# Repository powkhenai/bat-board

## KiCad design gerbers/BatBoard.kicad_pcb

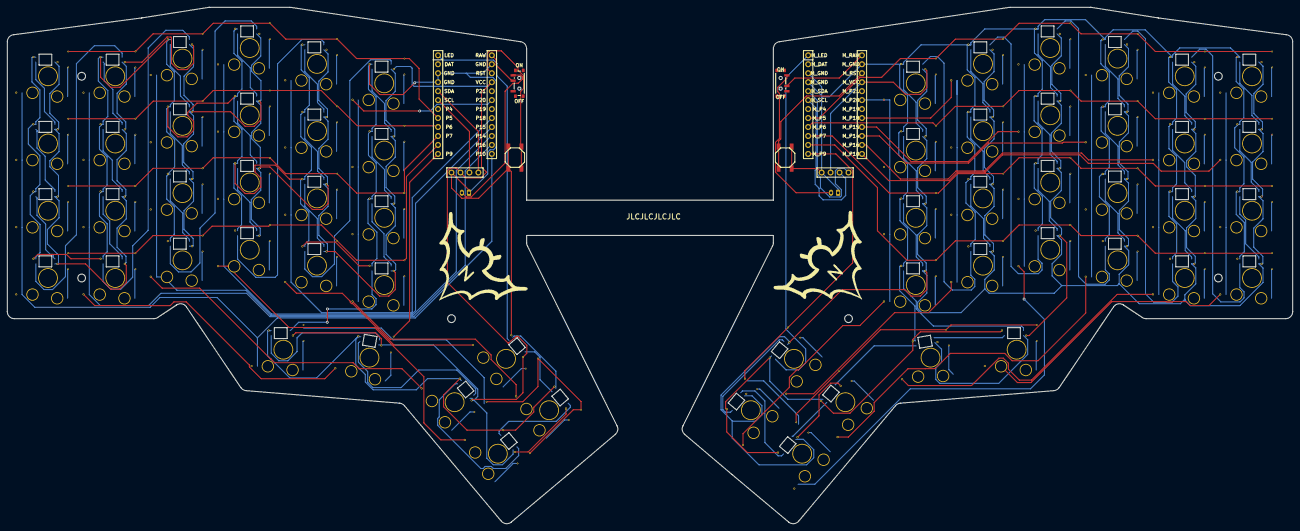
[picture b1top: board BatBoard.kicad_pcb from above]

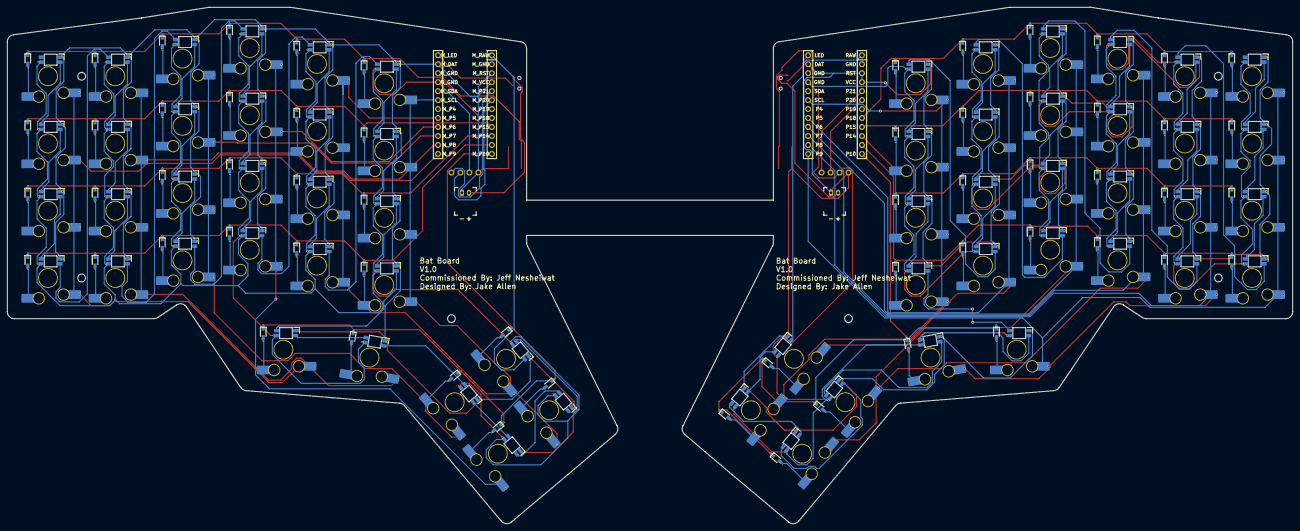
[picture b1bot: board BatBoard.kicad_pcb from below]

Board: 2 copper layers, 364.1 x 146.3 mm, 196 parts (182 on the bottom side), 156 nets.

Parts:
B1, B2: SW_TACT_ALPS_SKQGABE010
D1, D2, D3, D4, D5, D6, D7, D8, D9, D10, D11, D12, D13, D14, D15, D16, D17, D18, D19, D20, D21, D22, D23, D24, D25, D26, D27, D28, D29, D30, D31, D32, D33, D34, D35, D36, D37, D38, D39, D40, D41, D42, D43, D44, D45, D46, D47, D48, D49, D50, D51, D52, D53, D54, D55, D56, D57, D58, D59, D60: D_0805
DISP1, DISP2: display_ssd1306
JST1, JST2: ceoloide/battery_connector_jst_ph_2
LED1, LED2, LED3, LED4, LED5, LED6, LED7, LED8, LED9, LED10, LED11, LED12, LED13, LED14, LED15, LED16, LED17, LED18, LED19, LED20, LED21, LED22, LED23, LED24, LED25, LED26, LED27, LED28, LED29, LED30, LED31, LED32, LED33, LED34, LED35, LED36, LED37, LED38, LED39, LED40, LED41, LED42, LED43, LED44, LED45, LED46, LED47, LED48, LED49, LED50, LED51, LED52, LED53, LED54, LED55, LED56, LED57, LED58, LED59, LED60: led_SK6812mini-e (per-keysingle-side)
MCU1, MCU2: mcu_nice_nano
MH1, MH2, MH3, MH4, MH5, MH6: mounting_hole_npth
PWR1, PWR2: reset_button; power_switch_smd_side
S1, S2, S3, S4, S5, S6, S7, S8, S9, S10, S11, S12, S13, S14, S15, S16, S17, S18, S19, S20, S21, S22, S23, S24, S25, S26, S27, S28, S29, S30, S31, S32, S33, S34, S35, S36, S37, S38, S39, S40, S41, S42, S43, S44, S45, S46, S47, S48, S49, S50, S51, S52, S53, S54, S55, S56, S57, S58, S59, S60: switch_gateron_ks27_ks33

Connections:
BAT_P: JST1.2, PWR1.3
GND: B1.1, DISP1.1, JST1.1, LED1.3, LED2.3, LED3.3, LED4.3, LED5.3, LED6.3, LED7.3, LED8.3, LED9.3, LED10.3, LED11.3, LED12.3, LED13.3, LED14.3, LED15.3, LED16.3, LED17.3, LED18.3, LED19.3, LED20.3, LED21.3, LED22.3, LED23.3, LED24.3, LED25.3, LED26.3, LED27.3, LED28.3, LED29.3, LED30.3, MCU1.2, MCU1.21, MCU1.22
LED: LED29.4, MCU1.24
LED_1: LED29.2, LED30.4
LED_2: LED28.4, LED30.2
LED_3: LED27.4, LED28.2
LED_4: LED26.4, LED27.2
LED_5: LED25.4, LED26.2
LED_6: LED21.4, LED25.2
LED_7: LED21.2, LED22.4
LED_8: LED22.2, LED23.4
LED_9: LED23.2, LED24.4
LED_10: LED17.4, LED24.2
LED_11: LED17.2, LED18.4
LED_12: LED18.2, LED19.4
LED_13: LED19.2, LED20.4
LED_14: LED13.4, LED20.2
LED_15: LED13.2, LED14.4
LED_16: LED14.2, LED15.4
LED_17: LED15.2, LED16.4
LED_18: LED9.4, LED16.2
LED_19: LED9.2, LED10.4
LED_20: LED10.2, LED11.4
LED_21: LED11.2, LED12.4
LED_22: LED5.4, LED12.2
LED_23: LED5.2, LED6.4
LED_24: LED6.2, LED7.4
LED_25: LED7.2, LED8.4
LED_26: LED1.4, LED8.2
LED_27: LED1.2, LED2.4
LED_28: LED2.2, LED3.4
LED_29: LED3.2, LED4.4
M_BAT_P: JST2.2, PWR2.1
M_GND: B2.1, DISP2.1, JST2.1, LED31.3, LED32.3, LED33.3, LED34.3, LED35.3, LED36.3, LED37.3, LED38.3, LED39.3, LED40.3, LED41.3, LED42.3, LED43.3, LED44.3, LED45.3, LED46.3, LED47.3, LED48.3, LED49.3, LED50.3, LED51.3, LED52.3, LED53.3, LED54.3, LED55.3, LED56.3, LED57.3, LED58.3, LED59.3, LED60.3, MCU2.2, MCU2.21, MCU2.22
M_LED: LED59.4, MCU2.24
M_LED_1: LED59.2, LED60.4
M_LED_2: LED58.4, LED60.2
M_LED_3: LED57.4, LED58.2
M_LED_4: LED56.4, LED57.2
M_LED_5: LED55.4, LED56.2
M_LED_6: LED51.4, LED55.2
M_LED_7: LED51.2, LED52.4
M_LED_8: LED52.2, LED53.4
M_LED_9: LED53.2, LED54.4
M_LED_10: LED47.4, LED54.2
M_LED_11: LED47.2, LED48.4
M_LED_12: LED48.2, LED49.4
M_LED_13: LED49.2, LED50.4
M_LED_14: LED43.4, LED50.2
M_LED_15: LED43.2, LED44.4
M_LED_16: LED44.2, LED45.4
M_LED_17: LED45.2, LED46.4
M_LED_18: LED39.4, LED46.2
M_LED_19: LED39.2, LED40.4
M_LED_20: LED40.2, LED41.4
M_LED_21: LED41.2, LED42.4
M_LED_22: LED35.4, LED42.2
M_LED_23: LED35.2, LED36.4
M_LED_24: LED36.2, LED37.4
M_LED_25: LED37.2, LED38.4
M_LED_26: LED31.4, LED38.2
M_LED_27: LED31.2, LED32.4
M_LED_28: LED32.2, LED33.4
M_LED_29: LED33.2, LED34.4
M_P5: D34.1, D38.1, D42.1, D46.1, D50.1, D54.1, MCU2.17
M_P6: D33.1, D37.1, D41.1, D45.1, D49.1, D53.1, MCU2.16
M_P7: D32.1, D36.1, D40.1, D44.1, D48.1, D52.1, MCU2.15
M_P8: D31.1, D35.1, D39.1, D43.1, D47.1, D51.1, MCU2.14
M_P9: D55.1, D56.1, D57.1, D58.1, D59.1, D60.1, MCU2.13
M_P10: MCU2.12, S31.1, S32.1, S33.1, S34.1, S55.1
M_P14: MCU2.10, S39.1, S40.1, S41.1, S42.1, S57.1
M_P15: MCU2.9, S43.1, S44.1, S45.1, S46.1, S58.1
M_P16: MCU2.11, S35.1, S36.1, S37.1, S38.1, S56.1
M_P18: MCU2.8, S47.1, S48.1, S49.1, S50.1, S59.1
M_P20: MCU2.6, S51.1, S52.1, S53.1, S54.1, S60.1
M_RAW: MCU2.1, PWR2.2
M_RST: B2.2, MCU2.3
M_SCL: DISP2.3, MCU2.19
M_SDA: DISP2.4, MCU2.20
M_VCC: DISP2.2, LED31.1, LED32.1, LED33.1, LED34.1, LED35.1, LED36.1, LED37.1, LED38.1, LED39.1, LED40.1, LED41.1, LED42.1, LED43.1, LED44.1, LED45.1, LED46.1, LED47.1, LED48.1, LED49.1, LED50.1, LED51.1, LED52.1, LED53.1, LED54.1, LED55.1, LED56.1, LED57.1, LED58.1, LED59.1, LED60.1, MCU2.4
P5: D4.1, D8.1, D12.1, D16.1, D20.1, D24.1, MCU1.17
P6: D3.1, D7.1, D11.1, D15.1, D19.1, D23.1, MCU1.16
P7: D2.1, D6.1, D10.1, D14.1, D18.1, D22.1, MCU1.15
P8: D1.1, D5.1, D9.1, D13.1, D17.1, D21.1, MCU1.14
P9: D25.1, D26.1, D27.1, D28.1, D29.1, D30.1, MCU1.13
P10: MCU1.12, S1.1, S2.1, S3.1, S4.1, S25.1
P14: MCU1.10, S9.1, S10.1, S11.1, S12.1, S27.1
P15: MCU1.9, S13.1, S14.1, S15.1, S16.1, S28.1
P16: MCU1.11, S5.1, S6.1, S7.1, S8.1, S26.1
P18: MCU1.8, S17.1, S18.1, S19.1, S20.1, S29.1
P20: MCU1.6, S21.1, S22.1, S23.1, S24.1, S30.1
RAW: MCU1.1, PWR1.2
RST: B1.2, MCU1.3
SCL: DISP1.3, MCU1.19
SDA: DISP1.4, MCU1.20
VCC: DISP1.2, LED1.1, LED2.1, LED3.1, LED4.1, LED5.1, LED6.1, LED7.1, LED8.1, LED9.1, LED10.1, LED11.1, LED12.1, LED13.1, LED14.1, LED15.1, LED16.1, LED17.1, LED18.1, LED19.1, LED20.1, LED21.1, LED22.1, LED23.1, LED24.1, LED25.1, LED26.1, LED27.1, LED28.1, LED29.1, LED30.1, MCU1.4
extra_thumb: D29.2, S29.2
index_bottom: D17.2, S17.2
index_home: D18.2, S18.2
index_num: D20.2, S20.2
index_top: D19.2, S19.2
inner_bottom: D21.2, S21.2
inner_home: D22.2, S22.2
inner_num: D24.2, S24.2
inner_top: D23.2, S23.2
middle_bottom: D13.2, S13.2
middle_home: D14.2, S14.2
middle_num: D16.2, S16.2
middle_top: D15.2, S15.2
mirror_extra_thumb: D59.2, S59.2
mirror_index_bottom: D47.2, S47.2
mirror_index_home: D48.2, S48.2
mirror_index_num: D50.2, S50.2
mirror_index_top: D49.2, S49.2
mirror_inner_bottom: D51.2, S51.2
mirror_inner_home: D52.2, S52.2
mirror_inner_num: D54.2, S54.2
mirror_inner_top: D53.2, S53.2
mirror_middle_bottom: D43.2, S43.2
mirror_middle_home: D44.2, S44.2
mirror_middle_num: D46.2, S46.2
mirror_middle_top: D45.2, S45.2
mirror_outer_bottom: D31.2, S31.2
mirror_outer_home: D32.2, S32.2
mirror_outer_num: D34.2, S34.2
mirror_outer_top: D33.2, S33.2
mirror_pinky_bottom: D35.2, S35.2
mirror_pinky_home: D36.2, S36.2
mirror_pinky_num: D38.2, S38.2
mirror_pinky_top: D37.2, S37.2
mirror_plus_thumb: D60.2, S60.2
mirror_reachy_thumb: D58.2, S58.2
mirror_resty_thumb: D57.2, S57.2
mirror_ring_bottom: D39.2, S39.2
mirror_ring_home: D40.2, S40.2
mirror_ring_num: D42.2, S42.2
mirror_ring_top: D41.2, S41.2
mirror_stucky_thumb: D55.2, S55.2
mirror_tucky_thumb: D56.2, S56.2
outer_bottom: D1.2, S1.2
outer_home: D2.2, S2.2
outer_num: D4.2, S4.2
outer_top: D3.2, S3.2
pinky_bottom: D5.2, S5.2
pinky_home: D6.2, S6.2
pinky_num: D8.2, S8.2
pinky_top: D7.2, S7.2
plus_thumb: D30.2, S30.2
reachy_thumb: D28.2, S28.2
resty_thumb: D27.2, S27.2
ring_bottom: D9.2, S9.2
ring_home: D10.2, S10.2
ring_num: D12.2, S12.2
ring_top: D11.2, S11.2
stucky_thumb: D25.2, S25.2
tucky_thumb: D26.2, S26.2

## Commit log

2024-06-25 feat: a new module for a new board
2024-06-25 fix: remove errant comma
2024-06-25 fix: the keymap requires upper case letters for key descriptors
2024-06-25 chore: attempt underglow
2024-06-25 chore: attempt underglow part deux
2024-06-25 fix: match other zmk repos, and add another bobbin for RGB
2024-06-26 chore: fix a flub in the board overlay
2024-06-27 chore: try adding manual underglow toggle
2024-06-27 chore: fix typo in keymap
2024-06-27 chore: another iteration
2024-06-27 hack: upload gerber files to try to get help
2024-06-29 feat: enable oled display
2024-06-29 chore: iterate
2024-06-29 chore: try to get the conf file to stick
2024-06-29 chore: leds and display are working, now the keys are dead...
2024-06-29 chore: cleanup unneeded files and try to get keys working again
2024-06-29 fix: set correct height for oled
2024-06-29 fix: disable display to try to get keys working
2024-07-10 feat: change default underglow sequence to spectrum
2024-07-13 chore: try a firmware reset to get the right half working
2024-07-17 fix: fix the ctrl z issue
2024-07-17 fix: adjust cmd and opt keys to be in the more natural position
2024-07-20 Update bat_board.keymap
    minimum config and tutorial
2024-07-20 Update bat_board.keymap
    added bt select to number keys
2024-07-20 Update bat_board.keymap
    Adding MINUS
2024-07-20 Update bat_board.keymap
    moving backslash and adding apostrophe where it belongs
2025-03-21 chore: shuffle the repo around a bit for convenience and add split battery proxy
2025-04-01 fix: add mapping for cutting external power
2025-04-01 fix: index bt profiles from 0 as is clearly defined in the docs
2025-04-02 chore: add a Pow compatible layer
2025-04-02 fix: semicolons are hard
2025-04-02 fix: semicolons are VERY hard
2025-04-02 fix: move Pow friendly layer down the stack to allow proper layering
2025-04-04 feat: enable deep sleep for battery life perservation
2025-04-04 feat: attempt to enable studio support
2025-04-04 fix: use the correct header name
2025-04-04 fix: semi-colons are still hard
2025-04-04 fix: add unlock binding for using zmk studio
2025-04-07 fix: correct layout file to represent proper keys in proper locations
2025-04-10 chore: setup keymap as a default keymap for better use with studio
2025-04-10 fix: Change name for easier ble identification
2025-06-01 chore: adjust settings for original bat board
2025-06-01 fix: turn leds back on
2025-06-01 chore: troubleshoot leds
